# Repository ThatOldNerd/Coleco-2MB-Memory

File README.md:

# Coleco-2MB-Memory
Draft design of a Colecovision 2MB memory expander

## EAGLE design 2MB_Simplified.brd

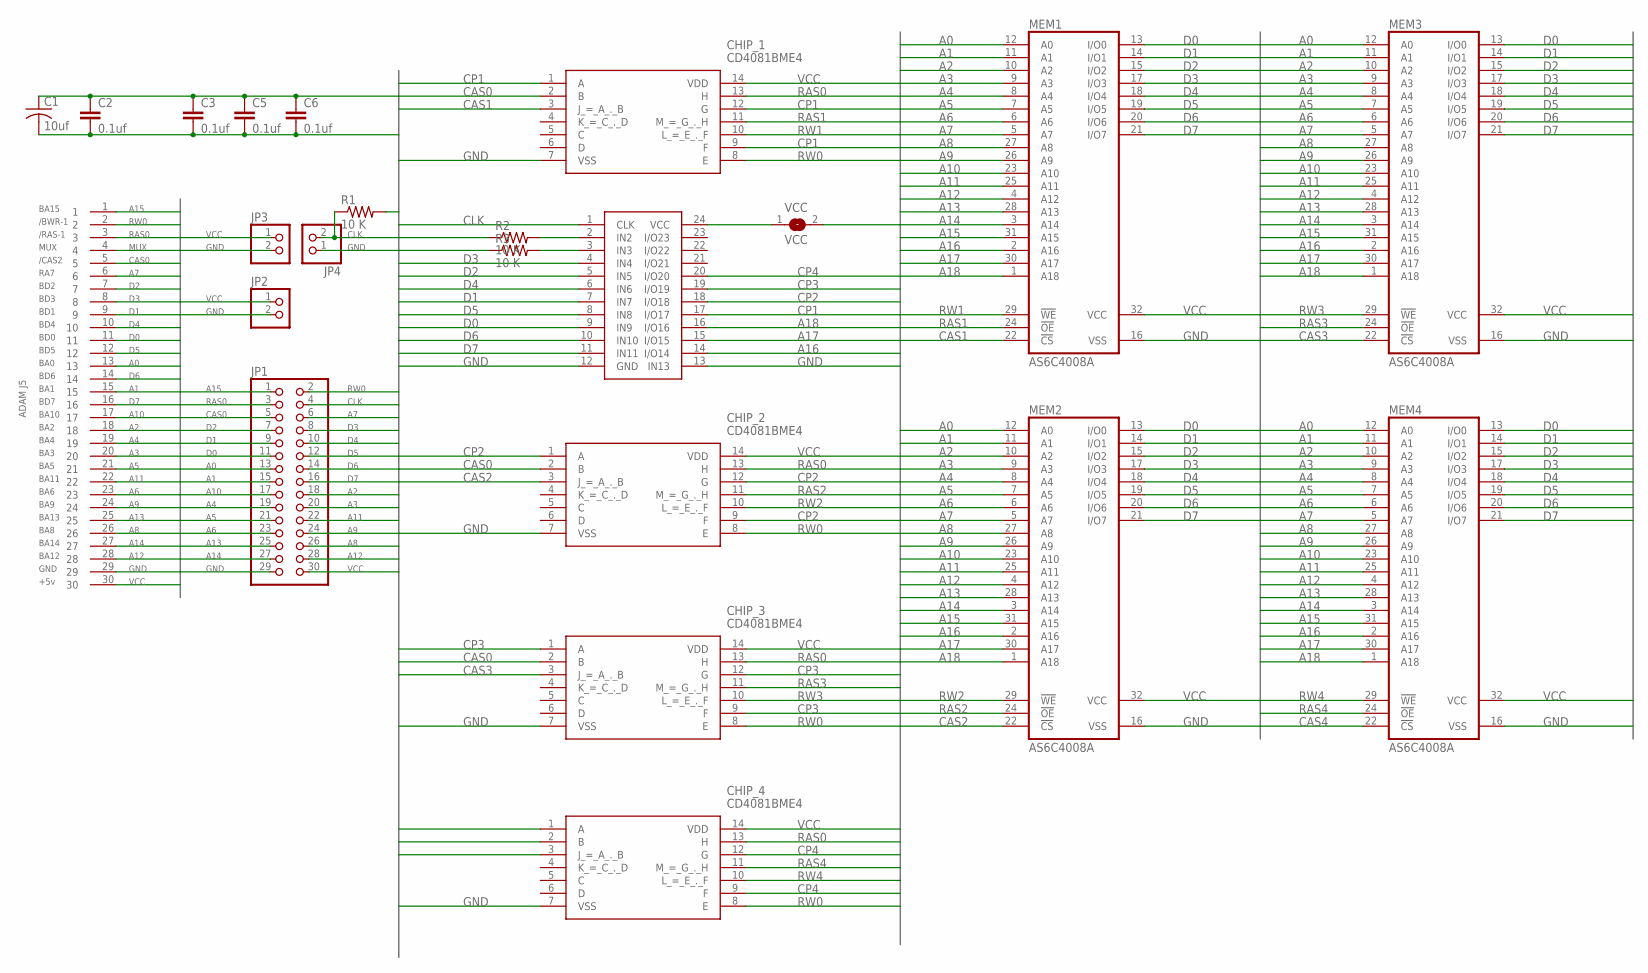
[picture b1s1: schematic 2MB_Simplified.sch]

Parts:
C1: 10uf; C050-025X075
C2, C3, C5, C6: 0.1uf; C1206
CHIP_1, CHIP_2, CHIP_3, CHIP_4: CD4081BME4; SOIC127P600X175-14N
JP1: PINHD-2X15; 2X15
JP2, JP3, JP4: PINHD-1X2; 1X02
MEM1, MEM2, MEM3, MEM4: AS6C4008A; SOP32-V2
R1, R2, R3: 10 K; M1206
U$3: J5CARD
U$6: ATF22V10; SO24W
VCC: VCC; SJ

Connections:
A0: JP1.13, MEM1.12 (A0), MEM2.12 (A0), MEM3.12 (A0), MEM4.12 (A0), U$3.13
A1: JP1.15, MEM1.11 (A1), MEM2.11 (A1), MEM3.11 (A1), MEM4.11 (A1), U$3.15
A2: JP1.18, MEM1.10 (A2), MEM2.10 (A2), MEM3.10 (A2), MEM4.10 (A2), U$3.18
A3: JP1.20, MEM1.9 (A3), MEM2.9 (A3), MEM3.9 (A3), MEM4.9 (A3), U$3.20
A4: JP1.19, MEM1.8 (A4), MEM2.8 (A4), MEM3.8 (A4), MEM4.8 (A4), U$3.19
A5: JP1.21, MEM1.7 (A5), MEM2.7 (A5), MEM3.7 (A5), MEM4.7 (A5), U$3.21
A6: JP1.23, MEM1.6 (A6), MEM2.6 (A6), MEM3.6 (A6), MEM4.6 (A6), U$3.23
A7: JP1.6, MEM1.5 (A7), MEM2.5 (A7), MEM3.5 (A7), MEM4.5 (A7), U$3.6
A8: JP1.26, MEM1.27 (A8), MEM2.27 (A8), MEM3.27 (A8), MEM4.27 (A8), U$3.26
A9: JP1.24, MEM1.26 (A9), MEM2.26 (A9), MEM3.26 (A9), MEM4.26 (A9), U$3.24
A10: JP1.17, MEM1.23 (A10), MEM2.23 (A10), MEM3.23 (A10), MEM4.23 (A10), U$3.17
A11: JP1.22, MEM1.25 (A11), MEM2.25 (A11), MEM3.25 (A11), MEM4.25 (A11), U$3.22
A12: JP1.28, MEM1.4 (A12), MEM2.4 (A12), MEM3.4 (A12), MEM4.4 (A12), U$3.28
A13: JP1.25, MEM1.28 (A13), MEM2.28 (A13), MEM3.28 (A13), MEM4.28 (A13), U$3.25
A14: JP1.27, MEM1.3 (A14), MEM2.3 (A14), MEM3.3 (A14), MEM4.3 (A14), U$3.27
A15: JP1.1, MEM1.31 (A15), MEM2.31 (A15), MEM3.31 (A15), MEM4.31 (A15), U$3.1
A16: MEM1.2 (A16), MEM2.2 (A16), MEM3.2 (A16), MEM4.2 (A16), U$6.14 (I/O14)
A17: MEM1.30 (A17), MEM2.30 (A17), MEM3.30 (A17), MEM4.30 (A17), U$6.15 (I/O15)
A18: MEM1.1 (A18), MEM2.1 (A18), MEM3.1 (A18), MEM4.1 (A18), U$6.16 (I/O16)
CAS0: CHIP_1.2 (B), CHIP_2.2 (B), CHIP_3.2 (B), CHIP_4.2 (B), JP1.5, U$3.5
CAS1: CHIP_1.3 (J_=_A_._B), MEM1.22 (!CS)
CAS2: CHIP_2.3 (J_=_A_._B), MEM2.22 (!CS)
CAS3: CHIP_3.3 (J_=_A_._B), MEM3.22 (!CS)
CAS4: CHIP_4.3 (J_=_A_._B), MEM4.22 (!CS)
CLK: JP1.4, JP4.2, R1.1, U$6.1 (CLK)
CP1: CHIP_1.1 (A), CHIP_1.9 (F), CHIP_1.12 (G), U$6.17 (I/O17)
CP2: CHIP_2.1 (A), CHIP_2.9 (F), CHIP_2.12 (G), U$6.18 (I/O18)
CP3: CHIP_3.1 (A), CHIP_3.9 (F), CHIP_3.12 (G), U$6.19 (I/O19)
CP4: CHIP_4.1 (A), CHIP_4.9 (F), CHIP_4.12 (G), U$6.20 (I/O20)
D0: JP1.11, MEM1.13 (I/O0), MEM2.13 (I/O0), MEM3.13 (I/O0), MEM4.13 (I/O0), U$3.11, U$6.9 (IN9)
D1: JP1.9, MEM1.14 (I/O1), MEM2.14 (I/O1), MEM3.14 (I/O1), MEM4.14 (I/O1), U$3.9, U$6.7 (IN7)
D2: JP1.7, MEM1.15 (I/O2), MEM2.15 (I/O2), MEM3.15 (I/O2), MEM4.15 (I/O2), U$3.7, U$6.5 (IN5)
D3: JP1.8, MEM1.17 (I/O3), MEM2.17 (I/O3), MEM3.17 (I/O3), MEM4.17 (I/O3), U$3.8, U$6.4 (IN4)
D4: JP1.10, MEM1.18 (I/O4), MEM2.18 (I/O4), MEM3.18 (I/O4), MEM4.18 (I/O4), U$3.10, U$6.6 (IN6)
D5: JP1.12, MEM1.19 (I/O5), MEM2.19 (I/O5), MEM3.19 (I/O5), MEM4.19 (I/O5), U$3.12, U$6.8 (IN8)
D6: JP1.14, MEM1.20 (I/O6), MEM2.20 (I/O6), MEM3.20 (I/O6), MEM4.20 (I/O6), U$3.14, U$6.10 (IN10)
D7: JP1.16, MEM1.21 (I/O7), MEM2.21 (I/O7), MEM3.21 (I/O7), MEM4.21 (I/O7), U$3.16, U$6.11 (IN11)
GND: C1.2, C2.2, C3.2, C5.2, C6.2, CHIP_1.7 (VSS), CHIP_2.7 (VSS), CHIP_3.7 (VSS), CHIP_4.7 (VSS), JP1.29, JP2.2, JP3.2, JP4.1, MEM1.16 (VSS), MEM2.16 (VSS), MEM3.16 (VSS), MEM4.16 (VSS), R1.2, R2.1, R3.1, U$3.29, U$6.12 (GND), U$6.13 (IN13)
MUX: U$3.4
unnamed: R2.2, U$6.2 (IN2)
unnamed: R3.2, U$6.3 (IN3)
unnamed: U$6.24 (VCC), VCC.1
RAS0: CHIP_1.13 (H), CHIP_2.13 (H), CHIP_3.13 (H), CHIP_4.13 (H), JP1.3, U$3.3
RAS1: CHIP_1.11 (M_=_G_._H), MEM1.24 (!OE)
RAS2: CHIP_2.11 (M_=_G_._H), MEM2.24 (!OE)
RAS3: CHIP_3.11 (M_=_G_._H), MEM3.24 (!OE)
RAS4: CHIP_4.11 (M_=_G_._H), MEM4.24 (!OE)
RW0: CHIP_1.8 (E), CHIP_2.8 (E), CHIP_3.8 (E), CHIP_4.8 (E), JP1.2, U$3.2
RW1: CHIP_1.10 (L_=_E_._F), MEM1.29 (!WE)
RW2: CHIP_2.10 (L_=_E_._F), MEM2.29 (!WE)
RW3: CHIP_3.10 (L_=_E_._F), MEM3.29 (!WE)
RW4: CHIP_4.10 (L_=_E_._F), MEM4.29 (!WE)
VCC: C1.1, C2.1, C3.1, C5.1, C6.1, CHIP_1.14 (VDD), CHIP_2.14 (VDD), CHIP_3.14 (VDD), CHIP_4.14 (VDD), JP1.30, JP2.1, JP3.1, MEM1.32 (VCC), MEM2.32 (VCC), MEM3.32 (VCC), MEM4.32 (VCC), U$3.30, VCC.2

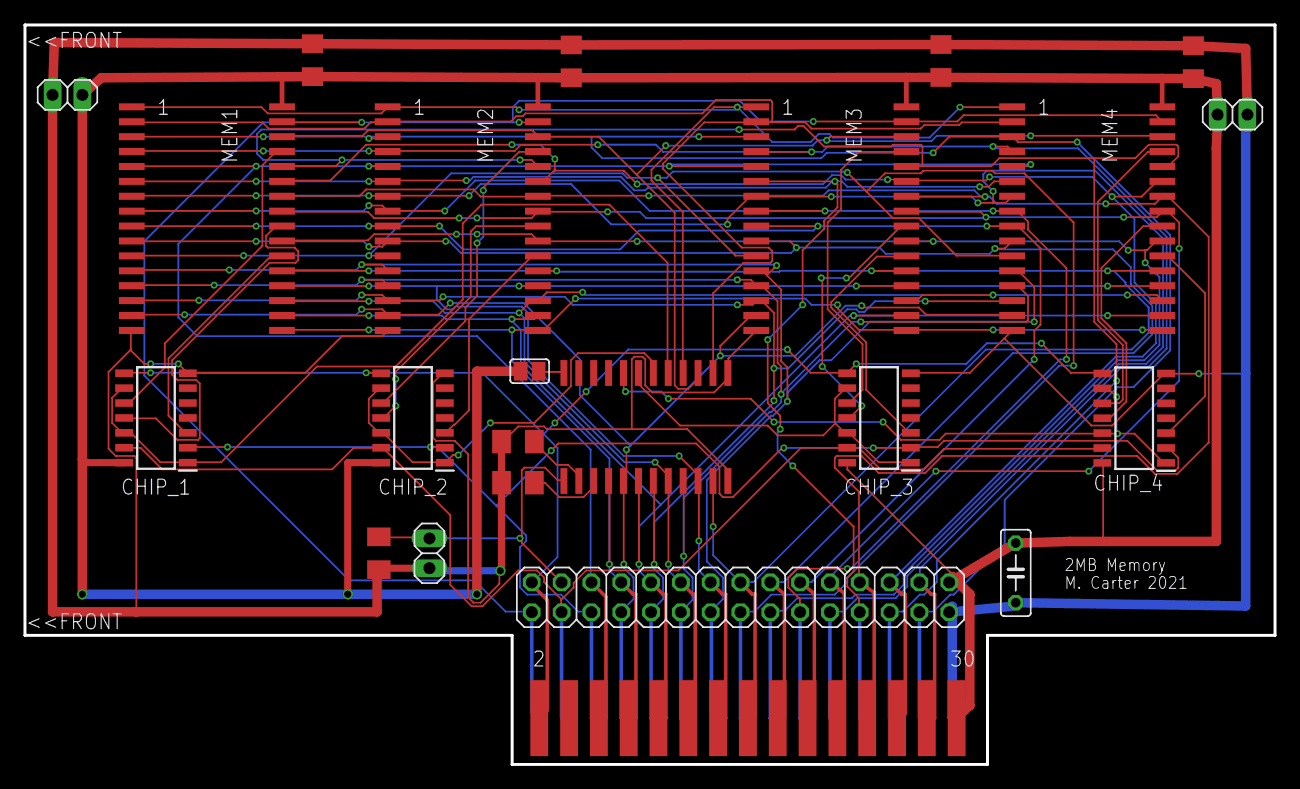
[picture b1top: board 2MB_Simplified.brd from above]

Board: 2 copper layers, 106.5 x 63.0 mm, 23 parts (0 on the bottom side), 52 nets.
